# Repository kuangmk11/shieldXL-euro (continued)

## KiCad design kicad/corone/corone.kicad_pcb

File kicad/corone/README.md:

# Corone

crow on a daughterboard for Moirae (shieldXL-euro). It runs monome's own
[crow firmware](https://github.com/monome/crow) unmodified, so the hardware
follows what that firmware drives. crow's hardware is closed: everything
below is read from the firmware source (`ll/`, `usbd/`, `Makefile`) or
worked out from it. Each item says which.

Corone plugs into the main board on one 2 x 10 header. The jacks are on the
main board, under the panel's CORONE outline; Corone carries the processor,
converters, analog stages and power.

## What the firmware fixes (read from source)

| | firmware | pins |
|---|---|---|
| MCU | STM32F722 (`-DSTM32F722xx`), 8 MHz HSE (`HSE_VALUE`), PLL to 216 MHz | |
| ADC | TI ADS131A0x, 2 channels enabled (`ADS_ADC_ENA 0x03`), 16-bit words, SPI1, MCLK from TIM2 CH4 | PA3 MCLK, PA4 NSS, PA5 SCK, PA6 MISO, PA7 MOSI, PC4 nRESET |
| DAC | TI DAC8565, quad 16-bit, on SPI2 run as I2S (24-bit frames, 48 kHz x 4 channels) | PB12 SYNC (I2S WS), PB13 SCLK, PB15 DIN, PB14 nRESET; I2S MCK out on PC6, unused |
| calibration mux | 3 select lines, 6 sources for input 1: outputs 4, 3, 2, 1, a 2.5 V reference, ground (codes 0-5). Ground at start-up | PC7 (A0), PC9 (A1), PC8 (A2) |
| ii | I2C1 | PB6 SCL, PB7 SDA |
| ii pull-ups | driven high from GPIO to switch them on, high-Z for off | PB3 (SCL pull-up), PB4 (SDA pull-up) |
| USB | OTG FS device, CDC serial, VBUS sensing on | PA11 D-, PA12 D+, PA9 VBUS |
| status LED | | PA15 |
| debug | USART3 | PC10 TX, PC11 RX; debug pin PB9 |

All of these fit the 64-pin STM32F722RET6 (LQFP-64), which is the part to use.

## Scaling (worked out from the firmware's conversions)

**Outputs.** `dac8565.c` writes `code = (2/3)·65535 − V·65535/15`. With the
DAC8565's internal 2.5 V reference, `Vdac = 5/3 − V/6`, so the output stage
must be

    Vout = 10 − 6·Vdac        (code 0 → +10 V, code 65535 → −5 V)

An inverting stage: Rin 20k, Rf 120k (gain −6), the + input at 10/7 V from
the 2.5 V reference through 30k / 40k (2.5 · 40/70 = 1.4286 V). Then 1k to
the jack. Precision quad op-amp on ±12 V (OPA4171 class).

**Inputs.** `ads131.c` reads `V = code·15/65535 + 2.5`, signed codes: full
scale ±32767 spans −5 V to +10 V around +2.5 V, and the comment confirms −5 V
reaches 0x8000. So the converter must see

    AINP − AINN = (Vin − 2.5) / 3      (±2.5 V full scale)

The firmware leaves A_SYS_CFG at reset, which selects an external reference:
REFP = 2.5 V (the DAC8565's reference output, buffered), REFN = GND. ADC on a
unipolar 5 V AVDD. One inverting stage per input, + input at 2.5 V, Rin 100k,
Rf 33.2k: its output `Vo = 2.5 − (Vin − 2.5)/3`, 0-5 V over −5…+10 V, goes to
AINN; AINP sits at the buffered 2.5 V. The inversion is undone by the choice
of pins, so the firmware's default scale (1.0) is right in sign. Series 1k
and clamps to AVDD / GND protect the converter when a jack is overdriven.
The exact gain is left to calibration.

**Calibration.** `calibrate.lua`: "cal.source(n) - set input[1] source to
output n", also `'gnd'` and `'2v5'`. Input 1's jack is normalled to the mux:
unpatched, it reads the selected source (ground, by default). So:

- The IN 1 jack's switch contact comes to Corone as its own header pin.
- The mux is an 8:1 on ±12 V with 3.3 V logic (ADG1208 / DG408 class).
- Sources 0-3 tap each output op-amp's output, before the 1k; source 4 is
  the 2.5 V reference; source 5 is ground; 6 and 7 are unused.
- Calibrating needs IN 1 unpatched, as on crow.

## Power

crow runs from the rack only ("60mA @ +12v, -15mA @ -12V, no 5V"); so does
Corone. +12 V → 5 V LDO (ADC AVDD, DAC) → 3.3 V LDO (MCU, ADC IOVDD). The
op-amps and mux on ±12 V. VBUS from the Pi is sensed, not used for power.

## Header to the main board (2 x 10, 2.54 mm)

| pin | signal | pin | signal |
|---|---|---|---|
| 1 | +12 V | 2 | −12 V |
| 3 | GND | 4 | GND |
| 5 | IN 1 tip | 6 | IN 1 normal (to the cal mux) |
| 7 | IN 2 tip | 8 | GND |
| 9 | OUT 1 | 10 | OUT 2 |
| 11 | OUT 3 | 12 | OUT 4 |
| 13 | GND | 14 | GND |
| 15 | USB D+ | 16 | USB D− |
| 17 | GND | 18 | VBUS (sense) |
| 19 | ii SCL | 20 | ii SDA |

The main board takes ii to a 3-pin header at its back edge, as crow has, and
USB from the Pi's fourth port, through J113 (see ../usb-adapter).

## Programming

- SWD pads (SWDIO, SWCLK, NRST, 3V3, GND) for the first flash.
- BOOT0 to a pad / button: the STM32 ROM DFU loader, for recovery.
- After that, crow's own bootloader (`submodules/dfu-stm32f7`) and its usual
  update path over USB.

## Placement

On the back of the main board, lower half, below the Pi (User.4 on the main
board marks about 60 x 45 mm of room). Stands about as tall as its header.

## Files

    corone.kicad_sch      the schematic - generated, do not edit by hand
    corone.kicad_sym      the ADS131A02 symbol (not in KiCad's library), from TI SBAS590E
    tools/make_corone.py  writes both; the part list and every pin's net are in it

`python3 tools/make_corone.py` rewrites them. ERC (`kicad-cli sch erc`): three
warnings, no errors - the GND power flag meets the mux's grounded spare
inputs, which KiCad types as bidirectional.

## Choices the firmware doesn't settle

- **ADC mode.** M0 open (synchronous slave): the firmware never reads DRDY
  and notes that pulling NSS low resyncs the filter. M1 open (16-bit words,
  as its comment says), M2 low (no Hamming code).
- **DAC reset.** RSTSEL high: the DAC8565 resets to mid-scale, so the jacks
  sit at +2.5 V until the firmware runs. Reset to zero would put +10 V on
  every output.
- **ii.** Pull-ups 2.2k from PB3 / PB4. The main board's ii header (J122)
  reads GND, SCL, SDA, the common order. There is no standard: monome's i2c
  guide says the order may be reversed between modules and to connect by
  name, finding GND by its marking - so J122's silkscreen should name all
  three pins and mark GND.
- **Power.** AMS1117-5.0 from +12 V carries the whole digital load (about
  0.5 W at 70 mA); give its tab copper.
- **VBUS.** Straight to PA9, as the firmware senses it there. With the rack
  off and the Pi on, 5 V sits on an unpowered pin; real crow on a norns
  sees the same.

## Open

- The input clamp, filter and exact resistor values: values above are the
  ideal; pick E96 and let calibration take up the rest.
- Output series resistor: 1k assumed.
- The ADS131A02 package (TQFP-32) and its CLK1/CLK2 settings match the
  firmware's 630 µs block; confirm the MCLK frequency from TIM2's period.

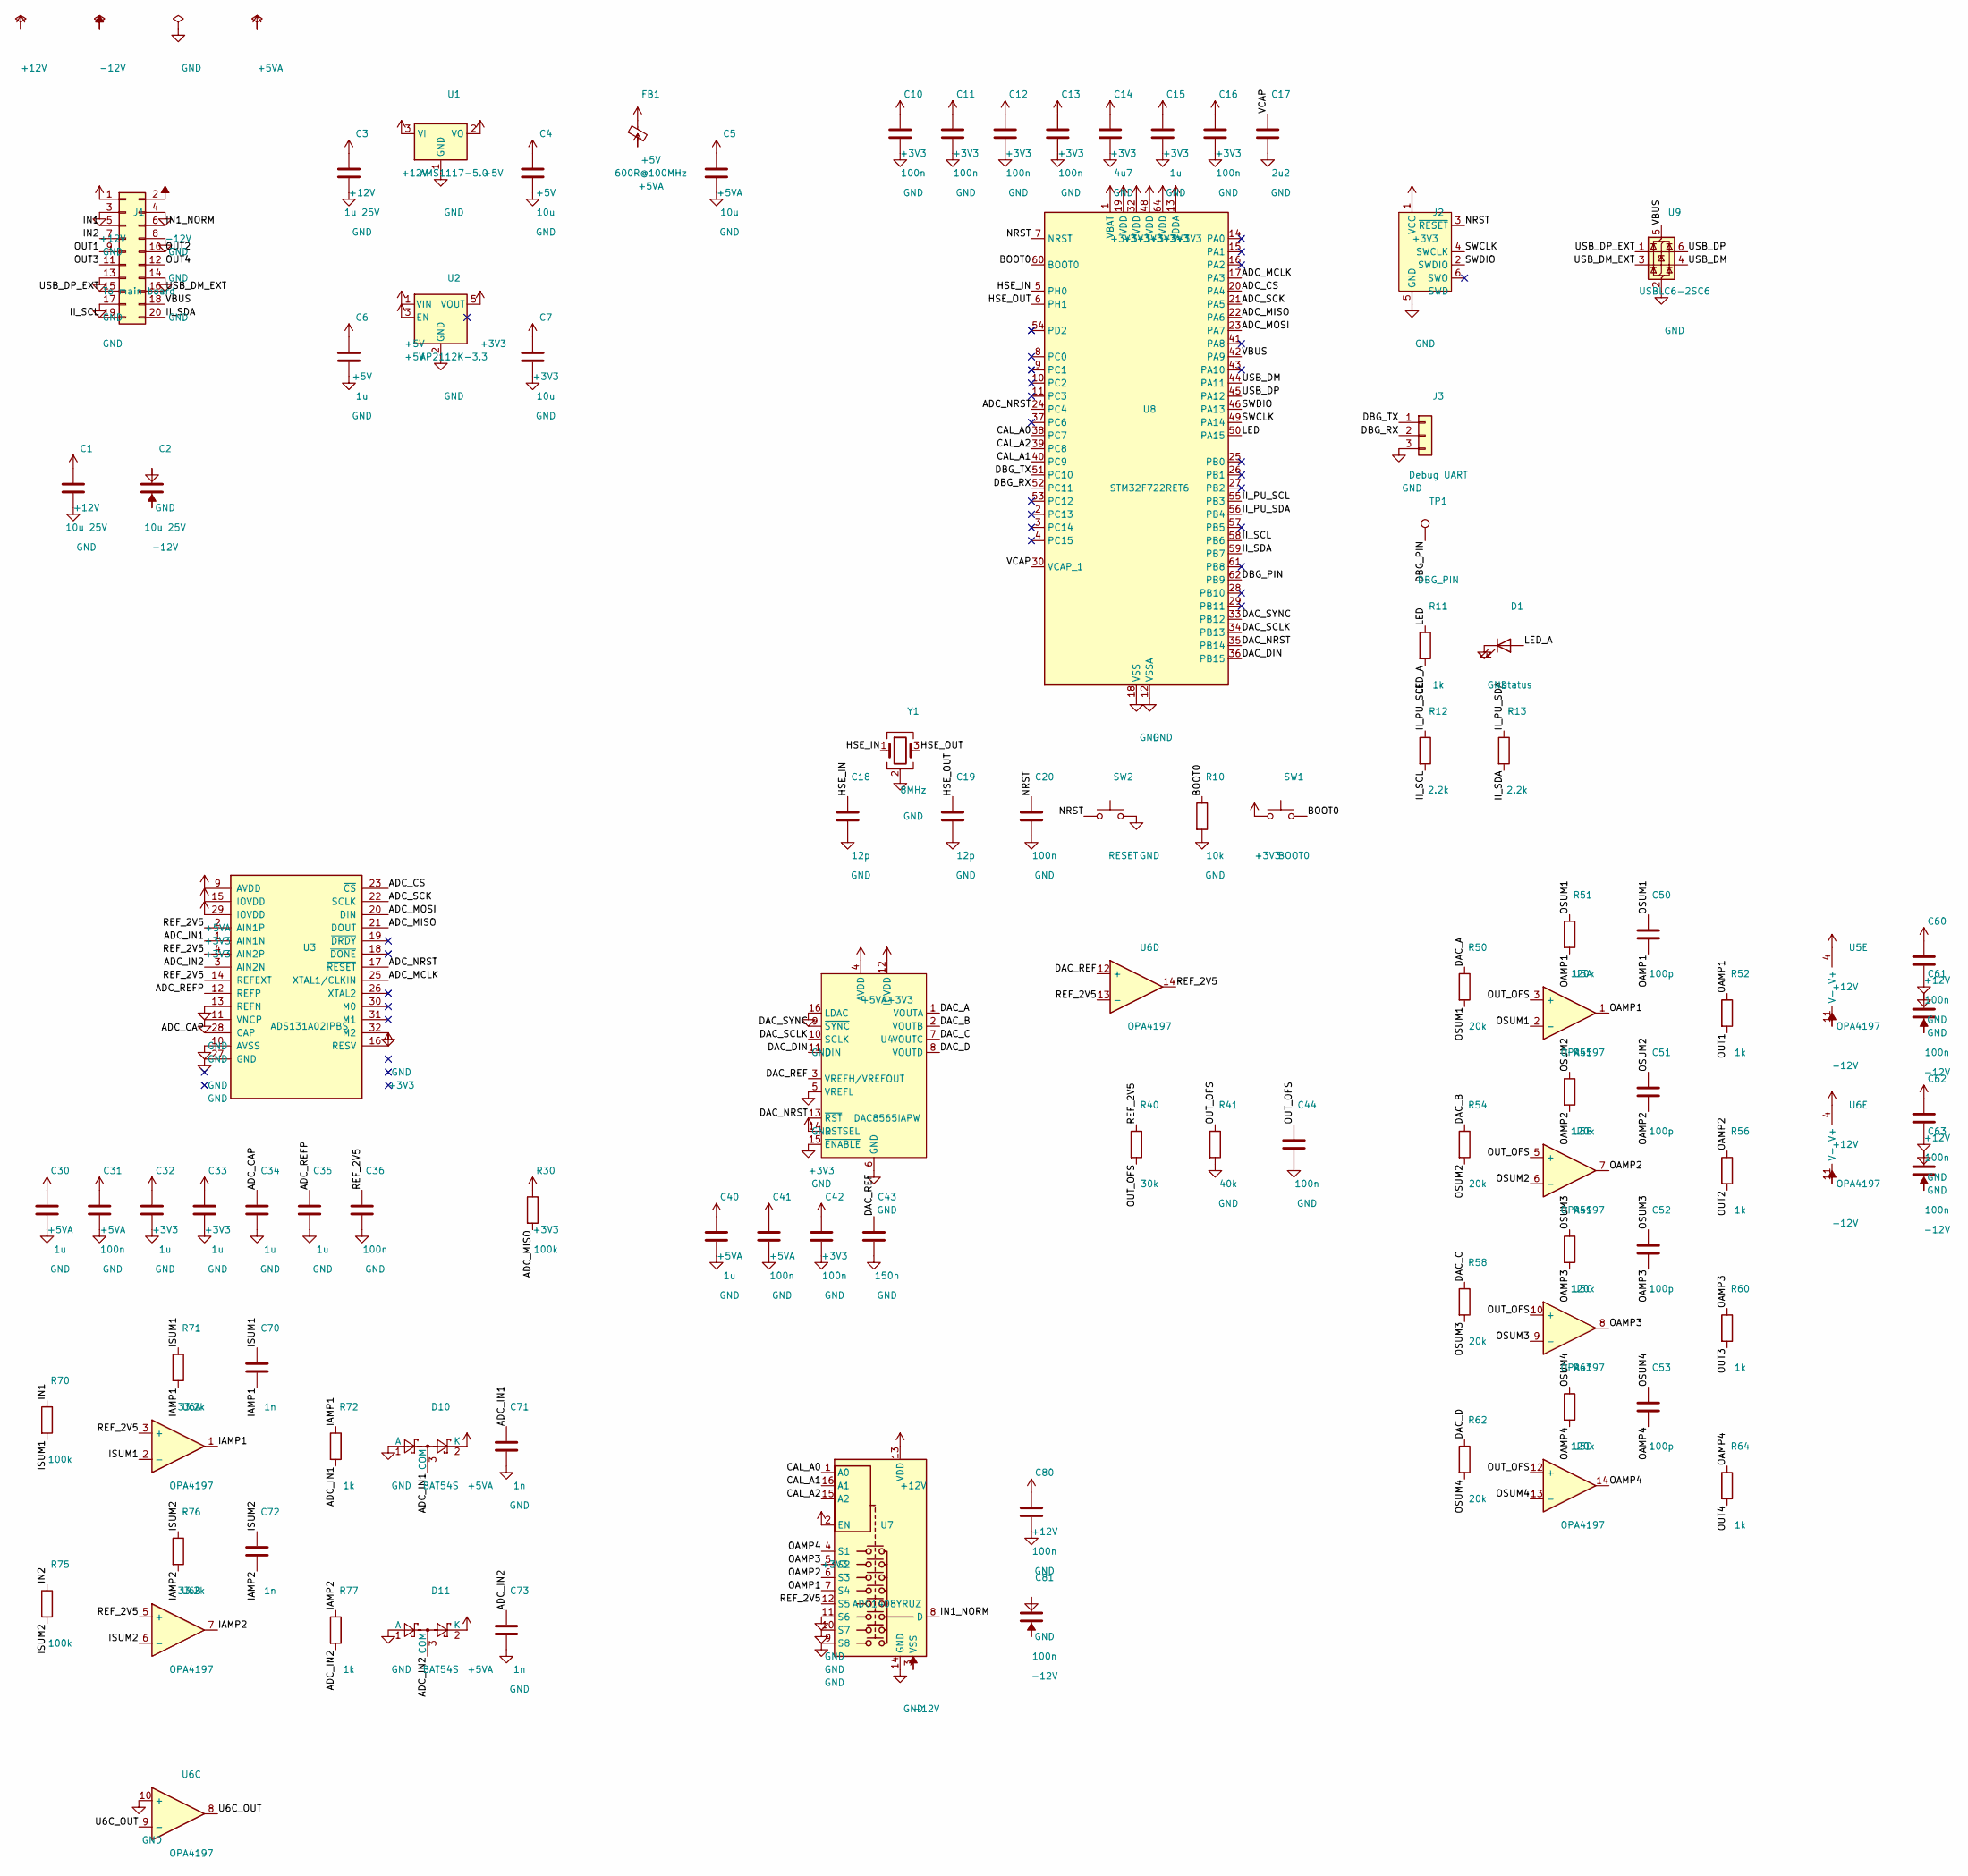
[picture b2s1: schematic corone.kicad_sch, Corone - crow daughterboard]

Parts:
C1, C2: 10u 25V; C_0805_2012Metric
C3: 1u 25V; C_0603_1608Metric
C4, C5, C7: 10u; C_0805_2012Metric
C6, C15, C30, C32, C33, C34, C35, C40: 1u; C_0603_1608Metric
C10, C11, C12, C13, C16, C20, C31, C36, C41, C42, C44, C60, C61, C62, C63, C80, C81: 100n; C_0603_1608Metric
C14: 4u7; C_0805_2012Metric
C17: 2u2; C_0603_1608Metric
C18, C19: 12p; C_0603_1608Metric
C43: 150n; C_0603_1608Metric
C50, C51, C52, C53: 100p; C_0603_1608Metric
C70, C71, C72, C73: 1n; C_0603_1608Metric
D1: status; LED_0603_1608Metric
D10, D11: BAT54S; SOT-23
FB1: 600R@100MHz; L_0603_1608Metric
J1: To main board; PinSocket_2x10_P2.54mm_Vertical
J2: SWD; Tag-Connect_TC2030-IDC-NL_2x03_P1.27mm_Vertical
J3: Debug UART; PinHeader_1x03_P2.54mm_Vertical
R10: 10k; R_0603_1608Metric
R11, R52, R56, R60, R64, R72, R77: 1k; R_0603_1608Metric
R12, R13: 2.2k; R_0603_1608Metric
R30, R70, R75: 100k; R_0603_1608Metric
R40: 30k; R_0603_1608Metric
R41: 40k; R_0603_1608Metric
R50, R54, R58, R62: 20k; R_0603_1608Metric
R51, R55, R59, R63: 120k; R_0603_1608Metric
R71, R76: 33.2k; R_0603_1608Metric
SW1: BOOT0; SW_SPST_TL3342
SW2: RESET; SW_SPST_TL3342
TP1: DBG_PIN; TestPoint_Pad_D1.0mm
U1: AMS1117-5.0; SOT-223-3_TabPin2
U2: AP2112K-3.3; SOT-23-5
U3: ADS131A02IPBS; TQFP-32_7x7mm_P0.8mm
U4: DAC8565IAPW; TSSOP-16_4.4x5mm_P0.65mm
U5, U6: OPA4197; TSSOP-14_4.4x5mm_P0.65mm
U7: ADG1408YRUZ; TSSOP-16_4.4x5mm_P0.65mm
U8: STM32F722RET6; LQFP-64_10x10mm_P0.5mm
U9: USBLC6-2SC6; SOT-23-6
Y1: 8MHz; Crystal_SMD_3225-4Pin_3.2x2.5mm

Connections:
+3V3: C7.1, C10.1, C11.1, C12.1, C13.1, C14.1, C15.1, C16.1, C32.1, C33.1, C42.1, J2.1 (VCC), R30.1, SW1.1, U2.5 (VOUT), U3.15 (IOVDD), U3.16 (RESV), U3.29 (IOVDD), U4.12 (IOVDD), U4.14 (RSTSEL), U7.2 (EN), U8.1 (VBAT), U8.13 (VDDA), U8.19 (VDD), U8.32 (VDD), U8.48 (VDD), U8.64 (VDD)
+5V: C4.1, C6.1, FB1.1, U1.2 (VO), U2.1 (VIN), U2.3 (EN)
+5VA: C5.1, C30.1, C31.1, C40.1, C41.1, D10.2 (K), D11.2 (K), FB1.2, U3.9 (AVDD), U4.4 (AVDD)
+12V: C1.1, C3.1, C60.1, C62.1, C80.1, J1.1, U1.3 (VI), U5.4 (V+), U6.4 (V+), U7.13 (VDD)
-12V: C2.2, C61.2, C63.2, C81.2, J1.2, U5.11 (V-), U6.11 (V-), U7.3 (VSS)
/ADC_CAP: C34.1, U3.28 (CAP)
/ADC_CS: U3.23 (~CS), U8.20 (PA4)
/ADC_IN1: C71.1, D10.3 (COM), R72.2, U3.1 (AIN1N)
/ADC_IN2: C73.1, D11.3 (COM), R77.2, U3.3 (AIN2N)
/ADC_MCLK: U3.25 (XTAL1/CLKIN), U8.17 (PA3)
/ADC_MISO: R30.2, U3.21 (DOUT), U8.22 (PA6)
/ADC_MOSI: U3.20 (DIN), U8.23 (PA7)
/ADC_NRST: U3.17 (~RESET), U8.24 (PC4)
/ADC_REFP: C35.1, U3.12 (REFP)
/ADC_SCK: U3.22 (SCLK), U8.21 (PA5)
/BOOT0: R10.1, SW1.2, U8.60 (BOOT0)
/CAL_A0: U7.1 (A0), U8.38 (PC7)
/CAL_A1: U7.16 (A1), U8.40 (PC9)
/CAL_A2: U7.15 (A2), U8.39 (PC8)
/DAC_A: R50.1, U4.1 (VOUTA)
/DAC_B: R54.1, U4.2 (VOUTB)
/DAC_C: R58.1, U4.7 (VOUTC)
/DAC_D: R62.1, U4.8 (VOUTD)
/DAC_DIN: U4.11 (DIN), U8.36 (PB15)
/DAC_NRST: U4.13 (~RST), U8.35 (PB14)
/DAC_REF: C43.1, U4.3 (VREFH/VREFOUT), U6.12 (+)
/DAC_SCLK: U4.10 (SCLK), U8.34 (PB13)
/DAC_SYNC: U4.9 (~SYNC), U8.33 (PB12)
/DBG_PIN: TP1.1 (1_1), U8.62 (PB9)
/DBG_RX: J3.2, U8.52 (PC11)
/DBG_TX: J3.1, U8.51 (PC10)
/HSE_IN: C18.1, U8.5 (PH0), Y1.1
/HSE_OUT: C19.1, U8.6 (PH1), Y1.3
/IAMP1: C70.2, R71.2, R72.1, U6.1
/IAMP2: C72.2, R76.2, R77.1, U6.7
/II_PU_SCL: R12.1, U8.55 (PB3)
/II_PU_SDA: R13.1, U8.56 (PB4)
/II_SCL: J1.19, R12.2, U8.58 (PB6)
/II_SDA: J1.20, R13.2, U8.59 (PB7)
/IN1: J1.5, R70.1
/IN1_NORM: J1.6, U7.8 (D)
/IN2: J1.7, R75.1
/ISUM1: C70.1, R70.2, R71.1, U6.2 (-)
/ISUM2: C72.1, R75.2, R76.1, U6.6 (-)
/LED: R11.1, U8.50 (PA15)
/LED_A: D1.2 (A), R11.2
/NRST: C20.1, J2.3 (~RESET), SW2.1, U8.7 (NRST)
/OAMP1: C50.2, R51.2, R52.1, U5.1, U7.7 (S4)
/OAMP2: C51.2, R55.2, R56.1, U5.7, U7.6 (S3)
/OAMP3: C52.2, R59.2, R60.1, U5.8, U7.5 (S2)
/OAMP4: C53.2, R63.2, R64.1, U5.14, U7.4 (S1)
/OSUM1: C50.1, R50.2, R51.1, U5.2 (-)
/OSUM2: C51.1, R54.2, R55.1, U5.6 (-)
/OSUM3: C52.1, R58.2, R59.1, U5.9 (-)
/OSUM4: C53.1, R62.2, R63.1, U5.13 (-)
/OUT1: J1.9, R52.2
/OUT2: J1.10, R56.2
/OUT3: J1.11, R60.2
/OUT4: J1.12, R64.2
/OUT_OFS: C44.1, R40.2, R41.1, U5.3 (+), U5.5 (+), U5.10 (+), U5.12 (+)
/REF_2V5: C36.1, R40.1, U3.2 (AIN1P), U3.4 (AIN2P), U3.14 (REFEXT), U6.3 (+), U6.5 (+), U6.13 (-), U6.14, U7.12 (S5)
/SWCLK: J2.4 (SWCLK), U8.49 (PA14)
/SWDIO: J2.2 (SWDIO), U8.46 (PA13)
/U6C_OUT: U6.8, U6.9 (-)
/USB_DM: U8.44 (PA11), U9.4 (I/O2)
/USB_DM_EXT: J1.16, U9.3 (I/O2)
/USB_DP: U8.45 (PA12), U9.6 (I/O1)
/USB_DP_EXT: J1.15, U9.1 (I/O1)
/VBUS: J1.18, U8.42 (PA9), U9.5 (VBUS)
/VCAP: C17.1, U8.30 (VCAP_1)
GND: C1.2, C2.1, C3.2, C4.2, C5.2, C6.2, C7.2, C10.2, C11.2, C12.2, C13.2, C14.2, C15.2, C16.2, C17.2, C18.2, C19.2, C20.2, C30.2, C31.2, C32.2, C33.2, C34.2, C35.2, C36.2, C40.2, C41.2, C42.2, C43.2, C44.2, C60.2, C61.1, C62.2, C63.1, C71.2, C73.2, C80.2, C81.1, D1.1 (K), D10.1 (A), D11.1 (A), J1.3, J1.4, J1.8, J1.13, J1.14, J1.17, J2.5 (GND), J3.3, R10.2, R41.2, SW2.2, U1.1 (GND), U2.2 (GND), U3.10 (AVSS), U3.11 (VNCP), U3.13 (REFN), U3.27 (GND), U3.32 (M2), U4.5 (VREFL), U4.6 (GND), U4.15 (~ENABLE), U4.16 (LDAC), U6.10 (+), U7.9 (S8), U7.10 (S7), U7.11 (S6), U7.14 (GND), U8.12 (VSSA), U8.18 (VSS), U8.31 (VSS), U8.47 (VSS), U8.63 (VSS), U9.2 (GND), Y1.2 (G), Y1.4 (G)

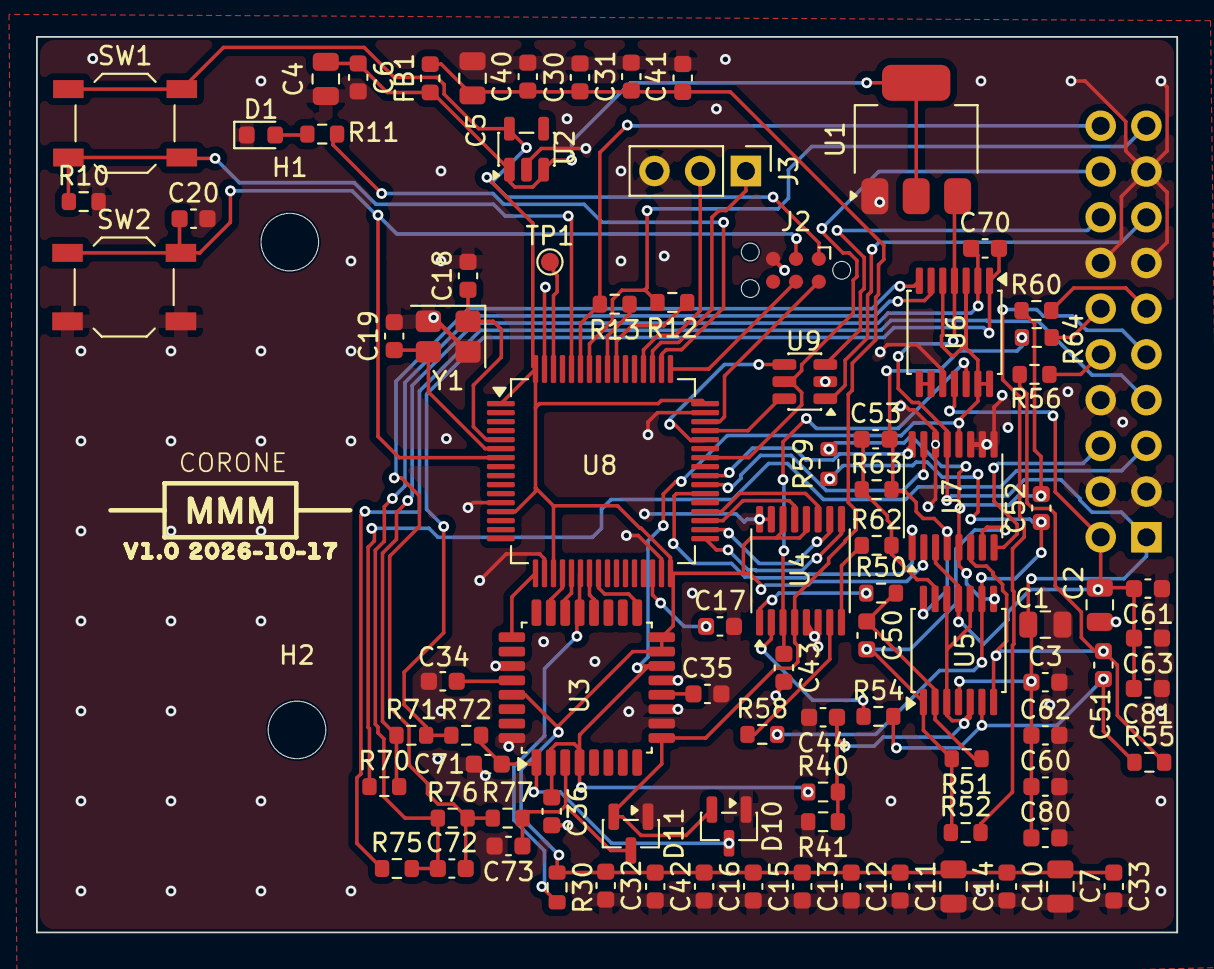
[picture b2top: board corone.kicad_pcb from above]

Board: 2 copper layers, 63.3 x 49.8 mm, 91 parts (1 on the bottom side), 71 nets.

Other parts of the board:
H1, H2: M3; MountingHole_3.2mm_M3

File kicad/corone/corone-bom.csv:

Refs,Qty,Value,Footprint,Manufacturer,MPN,DigiKey PN,DigiKey PN status,Notes
"C1,C2,C4,C5,C7",5,10u 25V / 10u,C_0805_2012Metric,Samsung,CL21A106KAYNNNE,1276-2891-1-ND,verified,
"C3,C6,C15,C30,C32-C35,C40",9,1u 25V / 1u,C_0603_1608Metric,Samsung,CL10A105KA8NNNC,,,
"C10-C13,C16,C20,C31,C36,C41,C42,C44,C60-C63,C80,C81",17,100n,C_0603_1608Metric,Samsung,CL10B104KB8NNNC,1276-1000-1-ND,verified,
C14,1,4u7,C_0805_2012Metric,Samsung,CL21A475KAQNNNE,,,
C17,1,2u2,C_0603_1608Metric,Samsung,CL10A225KO8NNNC,,,
"C18,C19",2,12p,C_0603_1608Metric,Samsung,CL10C120JB8NNNC,,,
C43,1,150n,C_0603_1608Metric,Samsung,CL10B154KA8NNNC,,,
C50-C53,4,100p,C_0603_1608Metric,Samsung,CL10C101JB8NNNC,,,
C70-C73,4,1n,C_0603_1608Metric,Samsung,CL10C102JB8NNNC,,,
D1,1,status,LED_0603_1608Metric,Lite-On,LTST-C191KRKT,,,
"D10,D11",2,BAT54S,SOT-23,Nexperia,"BAT54S,215",1727-2904-1-ND,verified,
FB1,1,600R@100MHz,L_0603_1608Metric,Murata,BLM18AG601SN1D,490-1014-1-ND,verified,
J1,1,To main board,PinSocket_2x10_P2.54mm_Vertical,Samtec,SSW-110-01-T-D,,,8.5 mm socket body (mates J121)
J2,1,SWD,Tag-Connect_TC2030-IDC-NL_2x03_P1.27mm_Vertical,Tag-Connect,(pads only - TC2030-IDC-NL cable),,,no part placed
J3,1,Debug UART,PinHeader_1x03_P2.54mm_Vertical,Sullins,PRPC003SAAN-RC,S1011EC-03-ND,pattern - confirm,
R10,1,10k,R_0603_1608Metric,Yageo,RC0603FR-0710KL,311-10.0KHRCT-ND,pattern - confirm,
"R11,R52,R56,R60,R64,R72,R77",7,1k,R_0603_1608Metric,Yageo,RC0603FR-071KL,311-1.00KHRCT-ND,pattern - confirm,
"R12,R13",2,2.2k,R_0603_1608Metric,Yageo,RC0603FR-072K2L,311-2.20KHRCT-ND,pattern - confirm,
"R30,R70,R75",3,100k,R_0603_1608Metric,Yageo,RC0603FR-07100KL,311-100KHRCT-ND,pattern - confirm,
R40,1,30k,R_0603_1608Metric,Yageo,RC0603FR-0730KL,311-30.0KHRCT-ND,pattern - confirm,
R41,1,40k,R_0603_1608Metric,Yageo,RC0603FR-0740K2L,311-40.2KHRCT-ND,pattern - confirm,40k is not a 1% value: 40.2k used - confirm against crow
"R50,R54,R58,R62",4,20k,R_0603_1608Metric,Yageo,RC0603FR-0720KL,311-20.0KHRCT-ND,pattern - confirm,
"R51,R55,R59,R63",4,120k,R_0603_1608Metric,Yageo,RC0603FR-07120KL,311-120KHRCT-ND,pattern - confirm,
"R71,R76",2,33.2k,R_0603_1608Metric,Yageo,RC0603FR-0733K2L,311-33.2KHRCT-ND,pattern - confirm,
"SW1,SW2",2,BOOT0 / RESET,SW_SPST_TL3342,E-Switch,TL3342F160QG/TR,EG2531CT-ND,pattern - confirm,
U1,1,AMS1117-5.0,SOT-223-3_TabPin2,Diodes,AZ1117CH-5.0TRG1,AZ1117CH-5.0TRG1DICT-ND,verified,AZ1117CH is the pin-compatible stocked equivalent
U2,1,AP2112K-3.3,SOT-23-5,Diodes,AP2112K-3.3TRG1,AP2112K-3.3TRG1DICT-ND,verified,
U3,1,ADS131A02IPBS,TQFP-32_7x7mm_P0.8mm,TI,ADS131A02IPBS,296-44812-ND,verified,
U4,1,DAC8565IAPW,TSSOP-16_4.4x5mm_P0.65mm,TI,DAC8565IAPW,296-22924-5-ND,verified,
"U5,U6",2,OPA4197,TSSOP-14_4.4x5mm_P0.65mm,TI,OPA4197IPWR,296-45060-1-ND,verified,
U7,1,ADG1408YRUZ,TSSOP-16_4.4x5mm_P0.65mm,Analog Devices,ADG1408YRUZ,505-ADG1408YRUZ-ND,verified,
U8,1,STM32F722RET6,LQFP-64_10x10mm_P0.5mm,ST,STM32F722RET6,497-17184-ND,verified,
U9,1,USBLC6-2SC6,SOT-23-6,ST,USBLC6-2SC6,497-5235-1-ND,verified,
Y1,1,8MHz,Crystal_SMD_3225-4Pin_3.2x2.5mm,,"8 MHz 3225 crystal, ~10 pF load (12 pF caps)",,,

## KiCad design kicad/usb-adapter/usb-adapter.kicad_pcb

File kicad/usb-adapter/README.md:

# Pi USB adapter

Brings the Pi 4's four USB ports to Moirae's main board. The Pi lies upside
down on the main board's back, ports toward the right edge; a small board
stands at each of its two USB stacks with two vertical male USB-A plugs, one
per port, and a 2 x 4 pin header whose IDC ribbon runs behind the Pi down to the main
board (J112 for the stack beside Ethernet, J113 for the outer one). The two
boards are identical.

    usb-adapter.kicad_sch                 generated - do not edit by hand
    usb-adapter.kicad_pcb                 routed by hand; the script only writes one if there is none
    usb-adapter.pretty                    the plug footprint, generated
    3d/USB_A_plug_placeholder.step        a 12 x 4.5 x 15 mm box standing in for the plug
    tools/make_usb_adapter.py             writes the rest (KiCad's Python)

In Moirae's 3D view, USBA1 / USBA2 on the main board carry this board as
../shieldXL-euro/3d/USB_adapter.step: rerun
../shieldXL-euro/tools/export_usb_adapter_step.sh after changing it.

    "/mnt/g/Program Files/KiCad/10.0/bin/python.exe" tools/make_usb_adapter.py

Board: 17.2 x 40 mm, standing at the port faces, from 5.3 to 45.3 mm off the
main board's back. The plugs face the Pi; so does the header, above the Pi's
underside, its ribbon running behind the Pi. Routed.

## Header pinout, in ribbon order

A plain 2 x 4 pin header here; a boxed 2 x 4 IDC (J112 / J113) on the main
board; an 8-way ribbon with IDC sockets between.

| pin | | pin | |
|---|---|---|---|
| 1 | VBUS A | 2 | GND |
| 3 | D- A | 4 | D+ A |
| 5 | GND | 6 | D- B |
| 7 | D+ B | 8 | VBUS B |

A is the port nearer the Pi's PCB, B the further one. Pair A rides between
grounds, pair B between ground and its VBUS.

## Before ordering

- **The plug.** A side-mount USB-A male, the "USB-71" (L = 15 mm short;
  Molex 48037 pattern), stood on its back end. `USB_A_Plug_Vertical` takes
  its four contact tails straight through, on the plug's centre line, in
  1.0 x 0.6 plated slots at the side-mount spacing (2.5 / 2.0 / 2.5), and its
  shell tabs in 0.9 x 4.0 plated slots at the jack's edges, 11.7 apart. The
  insert faces the Pi's PCB, where the Pi's tongue (along the top of each
  port) wants it. Its two bottom posts stand clear of the board; clip them
  or leave them. Check a sample's tails against the slots before ordering.
- **The plug spacing.** `PORT_ZC`, each port's centre above the Pi's PCB:
  3.49 and 12.63 (9.14 apart), read off the Pi 4 STEP model, where each
  opening is 5.1 mm tall with the port's tongue along its top. Check it with
  calipers on a real Pi.
- **The stack height.** `H`, the Pi's PCB above the main board's back, is
  20 mm, set by the 40-pin header and standoffs chosen for the main board.

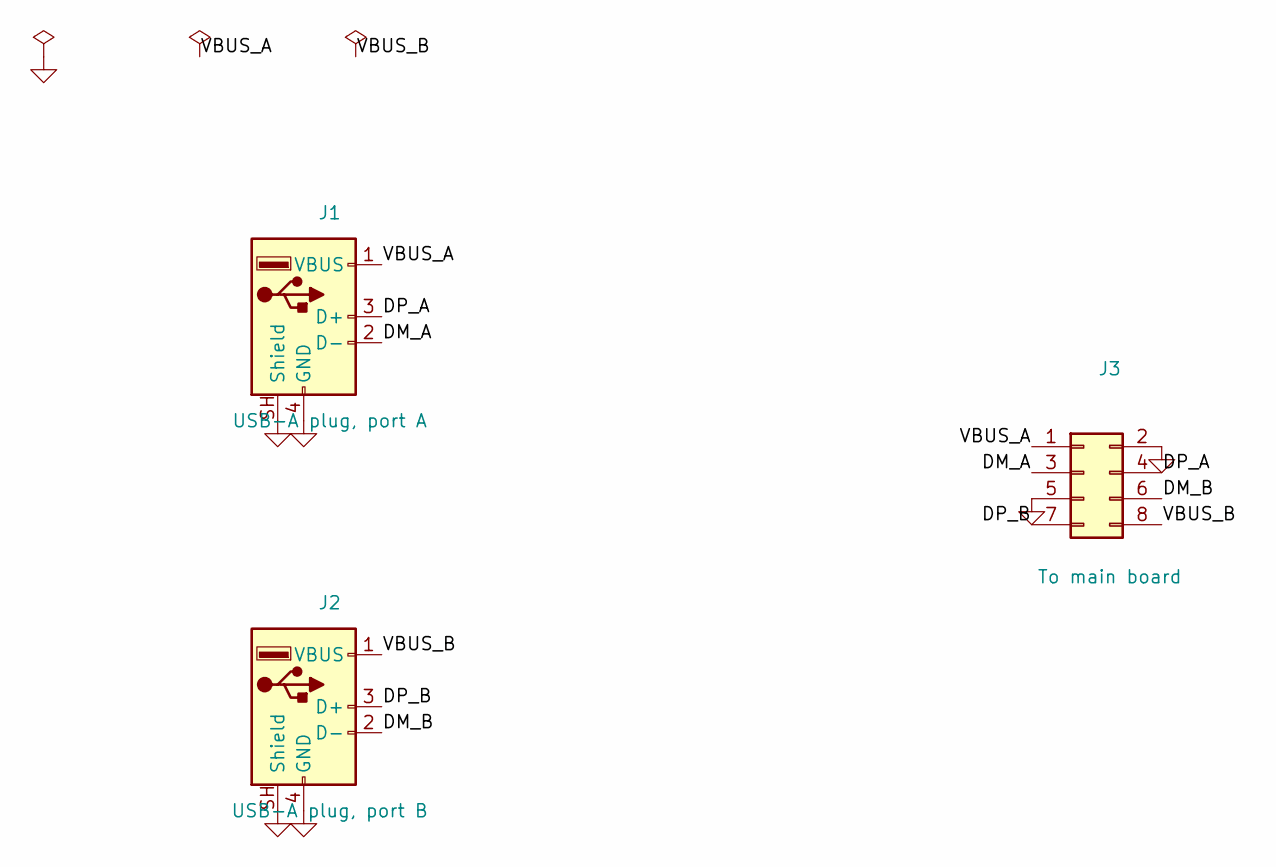
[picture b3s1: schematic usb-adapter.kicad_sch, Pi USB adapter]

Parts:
J1: USB-A plug, port A; USB_A_Plug_Vertical
J2: USB-A plug, port B; USB_A_Plug_Vertical
J3: To main board; PinHeader_2x04_P2.54mm_Vertical

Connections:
/DM_A: J1.2 (D-), J3.3
/DM_B: J2.2 (D-), J3.6
/DP_A: J1.3 (D+), J3.4
/DP_B: J2.3 (D+), J3.7
/VBUS_A: J1.1 (VBUS), J3.1
/VBUS_B: J2.1 (VBUS), J3.8
GND: J1.4 (GND), J1.SH (Shield), J2.4 (GND), J2.SH (Shield), J3.2, J3.5

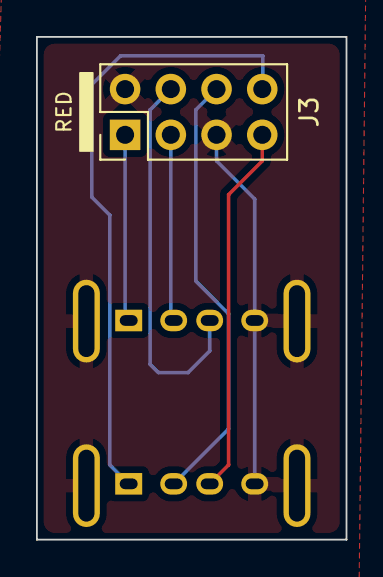
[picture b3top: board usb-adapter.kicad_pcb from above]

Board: 2 copper layers, 17.2 x 27.9 mm, 3 parts (0 on the bottom side), 7 nets.

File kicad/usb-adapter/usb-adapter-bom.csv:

Refs,Qty,Value,Footprint,Manufacturer,MPN,DigiKey PN,DigiKey PN status,Notes
"J1,J2",2,"USB-A plug, port A / USB-A plug, port B",USB_A_Plug_Vertical,generic,"USB-71 USB-A male, L=15 mm short",,,AliExpress; side-mount part stood on end
J3,1,To main board,PinHeader_2x04_P2.54mm_Vertical,Sullins,PRPC004DAAN-RC,,,

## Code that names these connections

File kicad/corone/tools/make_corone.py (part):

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Every pin assignment follows what crow's firmware drives (see ../README.md):

  MCU        U8 STM32F722RET6, 8 MHz crystal Y1, SWD on a TC2030 (J2),
             BOOT0 button SW1, reset button SW2, status LED D1 on PA15,
             debug USART3 on J3.
  ADC        U3 ADS131A02 on SPI1, clocked from TIM2 CH4 (PA3), synchronous
             slave (M0 open), 16-bit words (M1 open), no Hamming (M2 low),
             external 2.5 V reference on REFEXT.
  DAC        U4 DAC8565 on SPI2 as I2S, internal 2.5 V reference, resets to
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  cal mux    U7 ADG1408 on +-12 V: code 0-3 = outputs 4-1 (taken before the
             1k), 4 = REF_2V5, 5-7 = ground, onto IN1_NORM - input 1's
             jack switch, so an unpatched input 1 reads the selected source.
  ii         I2C1 on PB6 / PB7, pull-ups 2.2k switched by driving PB3 / PB4.
  USB        PA11 / PA12 through a USBLC6, VBUS sensed on PA9.
  power      +12 V -> AMS1117-5.0 -> +5V; +5V -> ferrite -> +5VA (ADC, DAC);
             +5V -> AP2112K-3.3 -> +3V3. Op-amps and mux on +-12 V. The rails
             arrive reverse-protected from the main board.
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        "44": "USB_DM", "45": "USB_DP", "46": "SWDIO", "47": "GND", "48": "+3V3", "49": "SWCLK",
        "50": "LED", "51": "DBG_TX", "52": "DBG_RX", "53": None, "54": None,
        "55": "II_PU_SCL", "56": "II_PU_SDA", "57": None, "58": "II_SCL", "59": "II_SDA",
        "60": "BOOT0", "61": None, "62": "DBG_PIN", "63": "GND", "64": "+3V3"}),
    C("C10", "100n", (195.58, 40.64), "+3V3", "GND"),
    C("C11", "100n", (205.74, 40.64), "+3V3", "GND"),
    C("C12", "100n", (215.9, 40.64), "+3V3", "GND"),
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     (297.18, 63.5), {"1": "+3V3", "2": "SWDIO", "3": "NRST", "4": "SWCLK", "5": "GND", "6": None}),
    ("J3", "Connector_Generic", "Conn_01x03", 1, "Debug UART", "Connector_PinHeader_2.54mm:PinHeader_1x03_P2.54mm_Vertical",
     (297.18, 99.06), {"1": "DBG_TX", "2": "DBG_RX", "3": "GND"}),
    ("TP1", "Connector", "TestPoint", 1, "DBG_PIN", "TestPoint:TestPoint_Pad_D1.0mm", (297.18, 119.38), {"1": "DBG_PIN"}),
    R("R11", "1k", (297.18, 139.7), "LED", "LED_A"),
    ("D1", "Device", "LED", 1, "status", "LED_SMD:LED_0603_1608Metric", (312.42, 139.7), {"2": "LED_A", "1": "GND"}),

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    R("R41", "40k", (256.54, 236.22), "OUT_OFS", "GND"),
    C("C44", "100n", (271.78, 236.22), "OUT_OFS", "GND"),
] + [
    p for k, (dac, unit, pins) in enumerate((("DAC_A", 1, ("3", "2", "1")), ("DAC_B", 2, ("5", "6", "7")),
                                             ("DAC_C", 3, ("10", "9", "8")), ("DAC_D", 4, ("12", "13", "14"))))
    for p in (
        R(f"R{50 + 4 * k}", "20k", (304.8, 205.74 + 30.48 * k), dac, f"OSUM{k + 1}"),
        R(f"R{51 + 4 * k}", "120k", (325.12, 195.58 + 30.48 * k), f"OSUM{k + 1}", f"OAMP{k + 1}"),
        C(f"C{50 + k}", "100p", (340.36, 195.58 + 30.48 * k), f"OSUM{k + 1}", f"OAMP{k + 1}"),
        amp("U5", unit, (325.12, 210.82 + 30.48 * k), {pins[0]: "OUT_OFS", pins[1]: f"OSUM{k + 1}", pins[2]: f"OAMP{k + 1}"}),
        R(f"R{52 + 4 * k}", "1k", (355.6, 210.82 + 30.48 * k), f"OAMP{k + 1}", f"OUT{k + 1}"),
    )
] + [
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        R(f"R{70 + 5 * k}", "100k", (30.48, 289.56 + 35.56 * k), f"IN{k + 1}", f"ISUM{k + 1}"),
        R(f"R{71 + 5 * k}", "33.2k", (55.88, 279.4 + 35.56 * k), f"ISUM{k + 1}", f"IAMP{k + 1}"),
        C(f"C{70 + 2 * k}", "1n", (71.12, 279.4 + 35.56 * k), f"ISUM{k + 1}", f"IAMP{k + 1}"),
        amp("U6", unit, (55.88, 294.64 + 35.56 * k), {pins[0]: "REF_2V5", pins[1]: f"ISUM{k + 1}", pins[2]: f"IAMP{k + 1}"}),
        R(f"R{72 + 5 * k}", "1k", (86.36, 294.64 + 35.56 * k), f"IAMP{k + 1}", f"ADC_IN{k + 1}"),
        ("D%d" % (10 + k), "Diode", "BAT54S", 1, "BAT54S", "Package_TO_SOT_SMD:SOT-23",
         (104.14, 294.64 + 35.56 * k), {"1": "GND", "2": "+5VA", "3": f"ADC_IN{k + 1}"}),
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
